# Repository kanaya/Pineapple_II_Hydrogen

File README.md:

# Pineapple II Hydrogen and Deuterium

## Description

Pineapple II Hydrogen (H) and Deuterium (2H) are a very simple MIDI sender/receiver. Pineapple II Hydrogen maps analog input from 0V to 5V to MIDI signal, and Pineapple II Deuterium converts MIDI signal to electrical status.

### Pineapple II Hydrogen (H)

### Pineapple II Deuterium (2H)

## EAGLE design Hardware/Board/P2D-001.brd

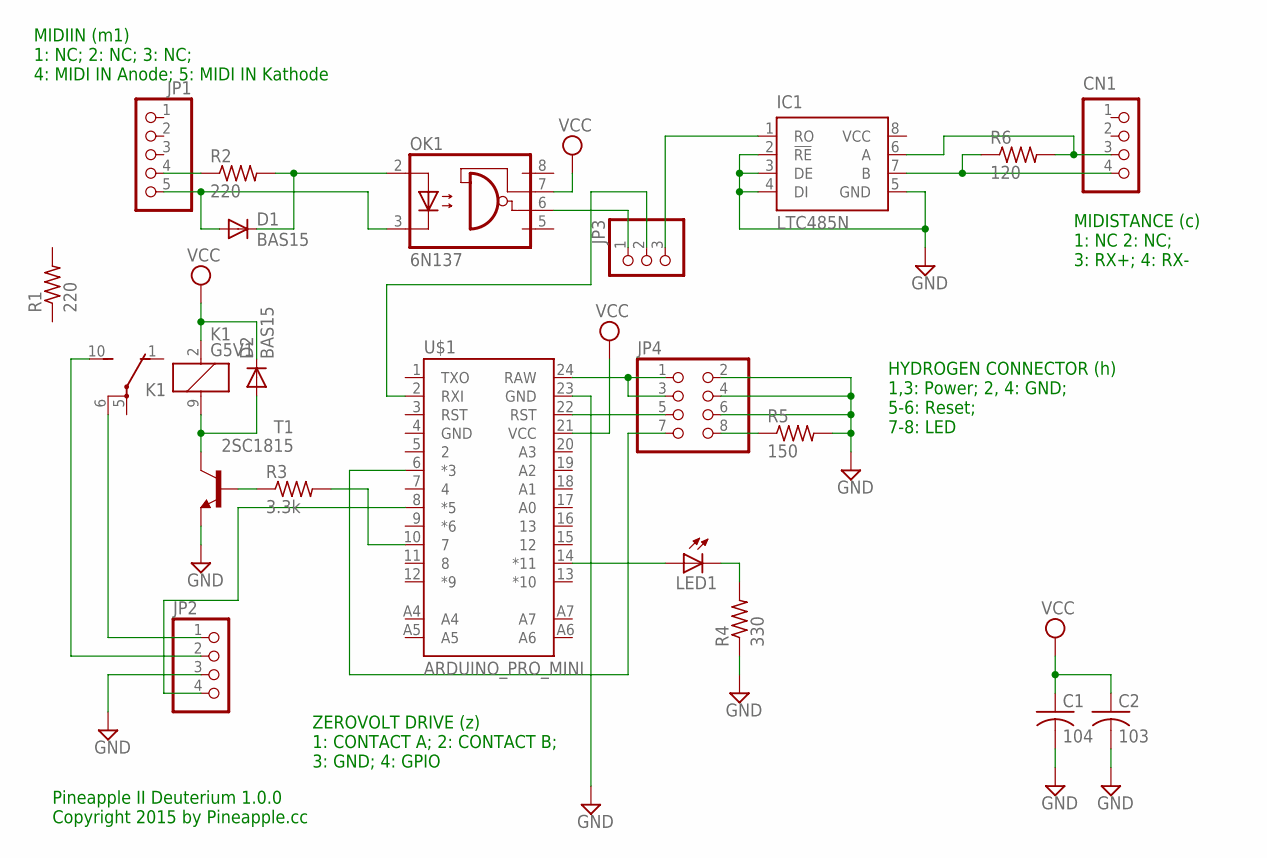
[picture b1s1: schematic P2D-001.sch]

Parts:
C1: 104; C025-025X050
C2: 103; C025-025X050
CN1: B4B-PH-K-S
D1, D2: BAS15; DO34-7
IC1: LTC485N; DIL08
JP1: PINHD-1X5; 1X05
JP2: PINHD-1X4; 1X04
JP3: PINHD-1X3; 1X03
JP4: PINHD-2X4; 2X04
K1: G5V1
LED1: LED3MM
OK1: 6N137; DIL08
R1, R2: 220; 0204/5
R3: 3.3k; 0204/5
R4: 330; 0204/5
R5: 150; 0204/5
R6: 120; 0204/5
T1: 2SC1815; TO92-ECB
U$1: ARDUINO_PRO_MINI

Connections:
GND: C1.2, C2.2, IC1.2 (!RE), IC1.3 (DE), IC1.4 (DI), IC1.5 (GND), JP2.3, JP4.2, JP4.4, JP4.6, R4.1, R5.2, T1.E, U$1.23 (GND)
unnamed: R3.2, U$1.10 (7)
unnamed: CN1.3, IC1.6 (A), R6.2
unnamed: JP1.4, R2.1
unnamed: D1.C, OK1.2 (A), R2.2
unnamed: JP4.8, R5.1
unnamed: JP4.5, U$1.22 (RST)
unnamed: D1.A, JP1.5, OK1.3 (C)
unnamed: JP4.7, U$1.6 (*3)
unnamed: JP4.1, JP4.3, U$1.24 (RAW)
unnamed: JP2.4, U$1.8 (*5)
unnamed: CN1.4, IC1.7 (B), R6.1
unnamed: JP3.1, OK1.6 (VO)
unnamed: R3.1, T1.B
unnamed: IC1.1 (RO), JP3.3
unnamed: D2.A, K1.9 (2), T1.C
unnamed: LED1.A, U$1.14 (*11)
unnamed: LED1.K (C), R4.2
unnamed: JP2.1, K1.6
unnamed: JP2.2, K1.10 (S)
unnamed: JP3.2, U$1.2 (RXI)
VCC: C1.1, C2.1, D2.C, K1.2 (1), OK1.7 (VE), U$1.21 (VCC)

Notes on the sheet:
Pineapple II Deuterium 1.0.0 Copyright 2015 by Pineapple.cc
MIDISTANCE (c) 1: NC 2: NC; 3: RX+; 4: RX-
MIDIIN (m1) 1: NC; 2: NC; 3: NC; 4: MIDI IN Anode; 5: MIDI IN Kathode
HYDROGEN CONNECTOR (h) 1,3: Power; 2, 4: GND; 5-6: Reset; 7-8: LED
ZEROVOLT DRIVE (z) 1: CONTACT A; 2: CONTACT B; 3: GND; 4: GPIO

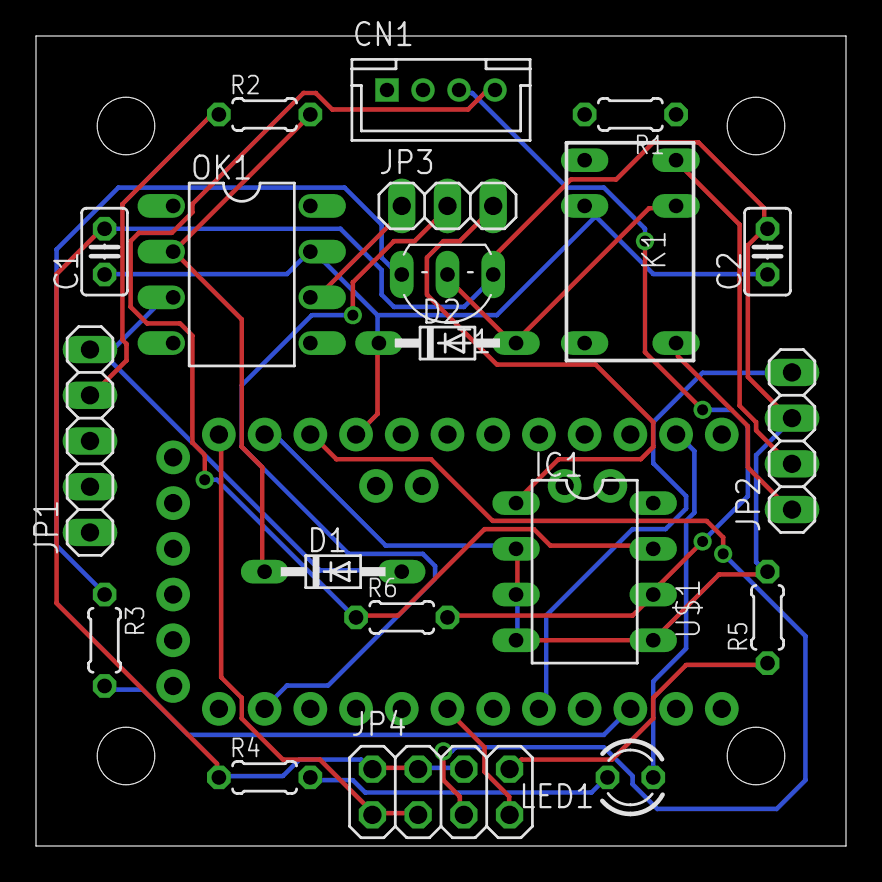
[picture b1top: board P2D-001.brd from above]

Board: 2 copper layers, 45.0 x 45.0 mm, 21 parts (0 on the bottom side), 22 nets.

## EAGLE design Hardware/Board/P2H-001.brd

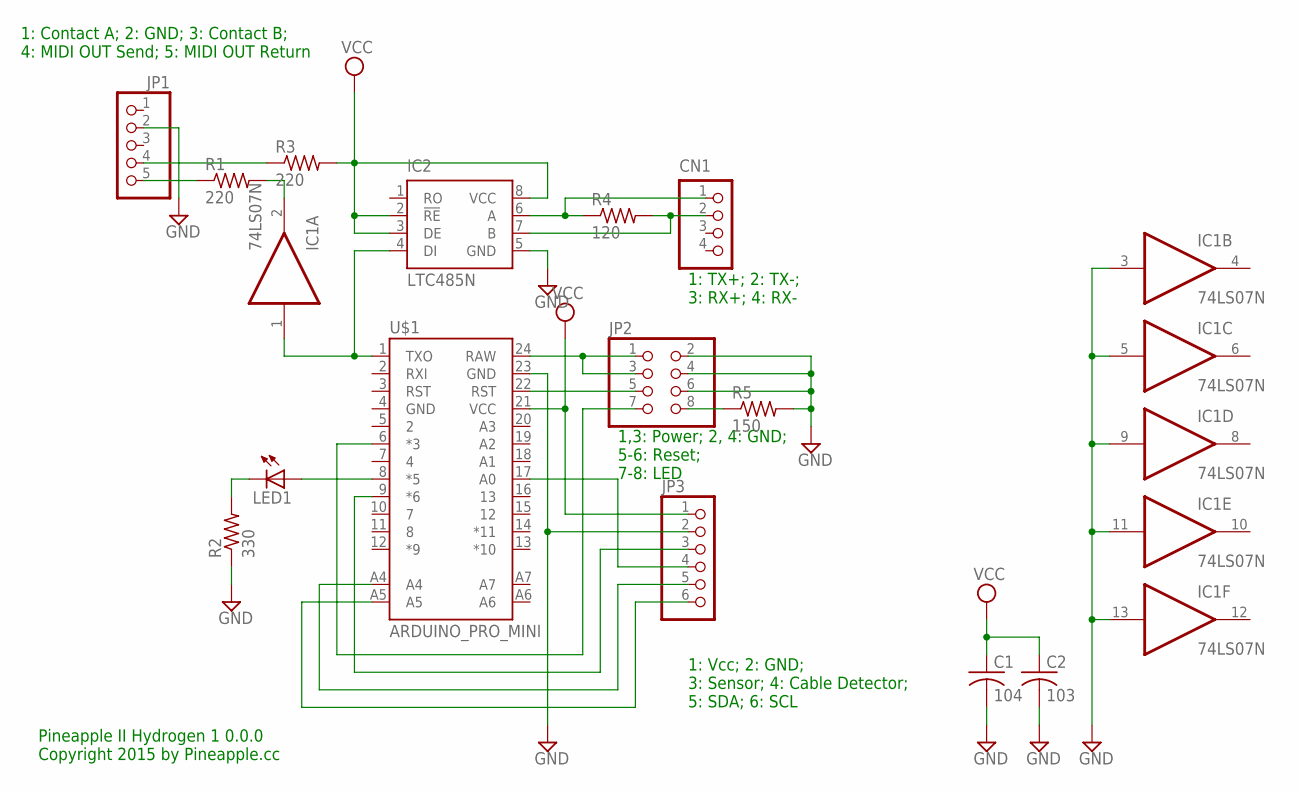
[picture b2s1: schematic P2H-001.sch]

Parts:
C1: 104; C025-025X050
C2: 103; C025-025X050
CN1: B4B-PH-K-S
IC1: 74LS07N; DIL14
IC2: LTC485N; DIL08
JP1: PINHD-1X5; 1X05
JP2: PINHD-2X4; 2X04
JP3: PINHD-1X6; 1X06
LED1: LED3MM
R1, R3: 220; 0204/5
R2: 330; 0204/5
R4: 120; 0204/5
R5: 150; 0204/5
U$1: ARDUINO_PRO_MINI

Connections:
GND: C1.2, C2.2, IC1.3 (I), IC1.5 (I), IC1.7 (GND), IC1.9 (I), IC1.11 (I), IC1.13 (I), IC2.5 (GND), JP1.2, JP2.2, JP2.4, JP2.6, JP3.2, R2.1, R5.2, U$1.23 (GND)
unnamed: IC1.1 (I), IC2.4 (DI), U$1.1 (TXO)
unnamed: IC1.2 (O), R1.2
unnamed: JP1.4, R3.1
unnamed: JP3.4, U$1.17 (A0)
unnamed: JP2.8, R5.1
unnamed: JP2.5, U$1.22 (RST)
unnamed: JP1.5, R1.1
unnamed: JP2.7, U$1.6 (*3)
unnamed: JP2.1, JP2.3, U$1.24 (RAW)
unnamed: JP3.3, U$1.9 (*6)
unnamed: JP3.5, U$1.A4
unnamed: LED1.A, U$1.8 (*5)
unnamed: LED1.K (C), R2.2
unnamed: JP3.6, U$1.A5
unnamed: CN1.1, IC2.6 (A), R4.1
unnamed: CN1.2, IC2.7 (B), R4.2
VCC: C1.1, C2.1, IC1.14 (VCC), IC2.2 (!RE), IC2.3 (DE), IC2.8 (VCC), JP3.1, R3.2, U$1.21 (VCC)

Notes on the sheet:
Pineapple II Hydrogen 1 0.0.0 Copyright 2015 by Pineapple.cc
1: TX+; 2: TX-; 3: RX+; 4: RX-
1: Contact A; 2: GND; 3: Contact B; 4: MIDI OUT Send; 5: MIDI OUT Return
1,3: Power; 2, 4: GND; 5-6: Reset; 7-8: LED
1: Vcc; 2: GND; 3: Sensor; 4: Cable Detector; 5: SDA; 6: SCL

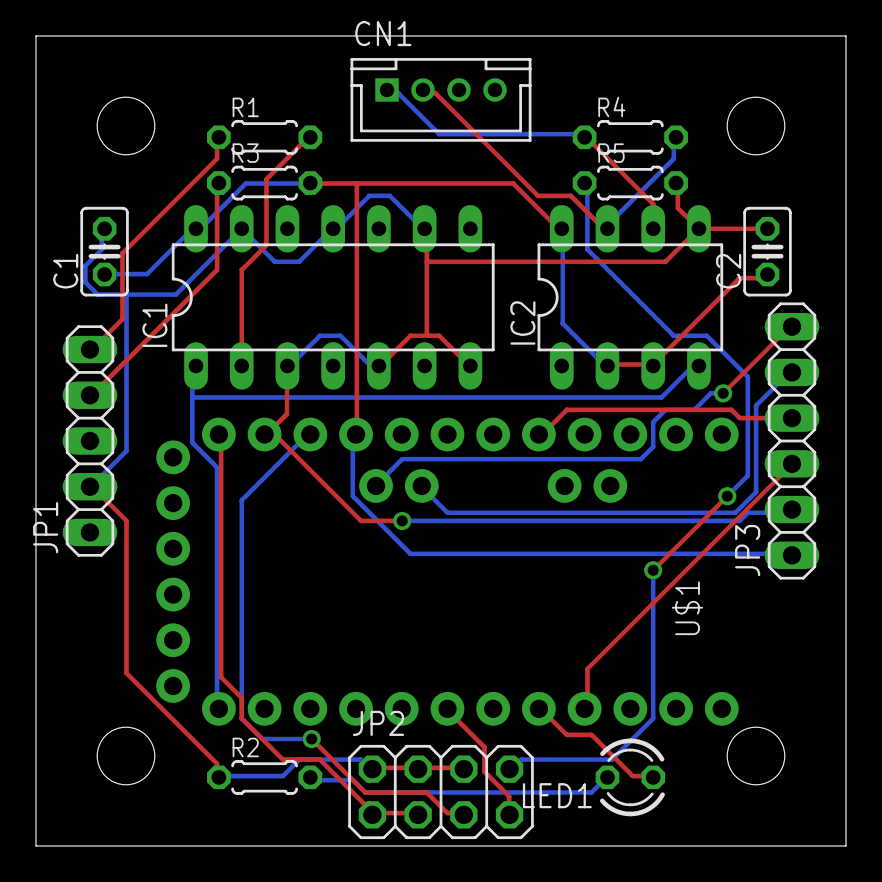
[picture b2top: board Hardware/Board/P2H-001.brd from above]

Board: 2 copper layers, 45.0 x 45.0 mm, 15 parts (0 on the bottom side), 18 nets.

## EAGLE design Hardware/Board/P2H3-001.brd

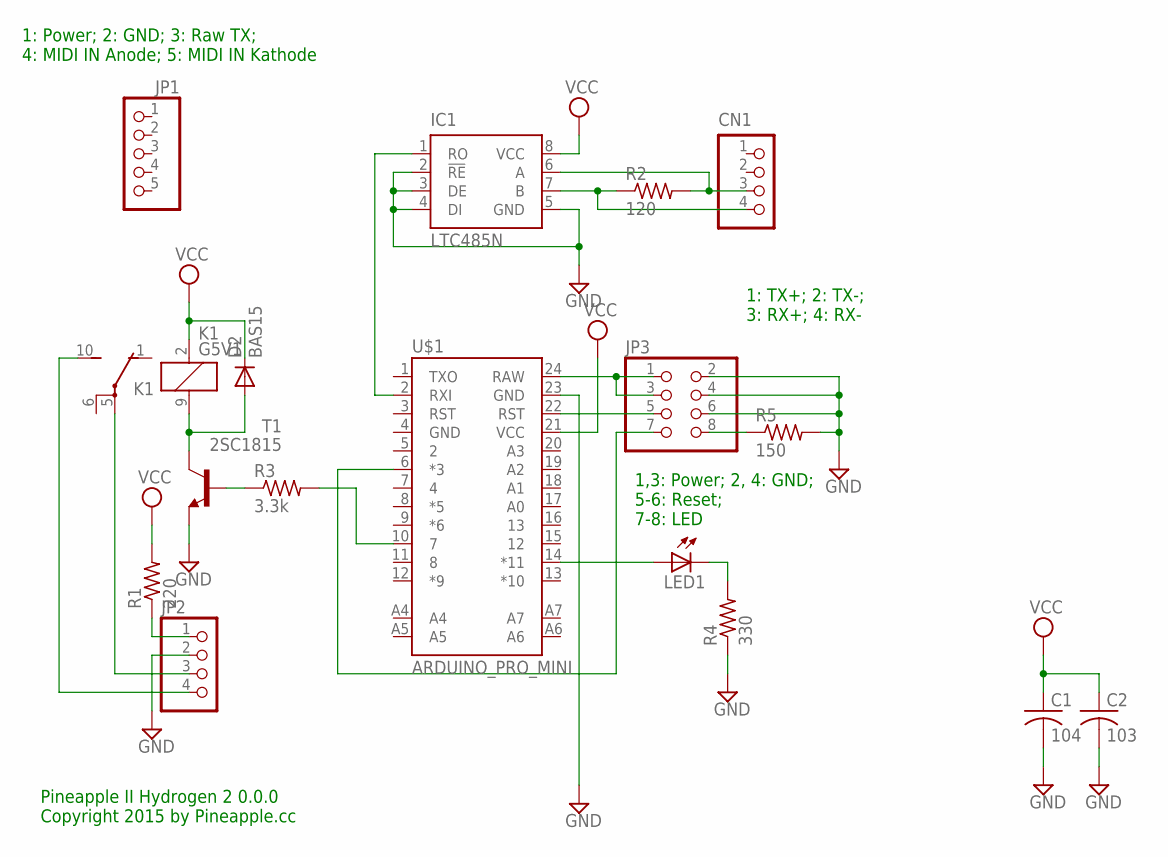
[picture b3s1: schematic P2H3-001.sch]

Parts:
C1: 104; C025-025X050
C2: 103; C025-025X050
CN1: B4B-PH-K-S
D2: BAS15; DO34-7
IC1: LTC485N; DIL08
JP1: PINHD-1X5; 1X05
JP2: PINHD-1X4; 1X04
JP3: PINHD-2X4; 2X04
K1: G5V1
LED1: LED3MM
R1: 220; 0204/5
R2: 120; 0204/5
R3: 3.3k; 0204/5
R4: 330; 0204/5
R5: 150; 0204/5
T1: 2SC1815; TO92-ECB
U$1: ARDUINO_PRO_MINI

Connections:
GND: C1.2, C2.2, IC1.2 (!RE), IC1.3 (DE), IC1.4 (DI), IC1.5 (GND), JP2.2, JP3.2, JP3.4, JP3.6, R4.1, R5.2, T1.E, U$1.23 (GND)
unnamed: R3.2, U$1.10 (7)
unnamed: CN1.3, IC1.6 (A), R2.2
unnamed: CN1.4, IC1.7 (B), R2.1
unnamed: JP3.8, R5.1
unnamed: JP3.5, U$1.22 (RST)
unnamed: JP3.7, U$1.6 (*3)
unnamed: JP3.1, JP3.3, U$1.24 (RAW)
unnamed: JP2.1, R1.1
unnamed: IC1.1 (RO), U$1.2 (RXI)
unnamed: R3.1, T1.B
unnamed: D2.A, K1.9 (2), T1.C
unnamed: LED1.A, U$1.14 (*11)
unnamed: LED1.K (C), R4.2
unnamed: JP2.3, K1.5
unnamed: JP2.4, K1.10 (S)
VCC: C1.1, C2.1, D2.C, IC1.8 (VCC), K1.2 (1), R1.2, U$1.21 (VCC)

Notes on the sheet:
Pineapple II Hydrogen 2 0.0.0 Copyright 2015 by Pineapple.cc
1: TX+; 2: TX-; 3: RX+; 4: RX-
1: Power; 2: GND; 3: Raw TX; 4: MIDI IN Anode; 5: MIDI IN Kathode
1,3: Power; 2, 4: GND; 5-6: Reset; 7-8: LED

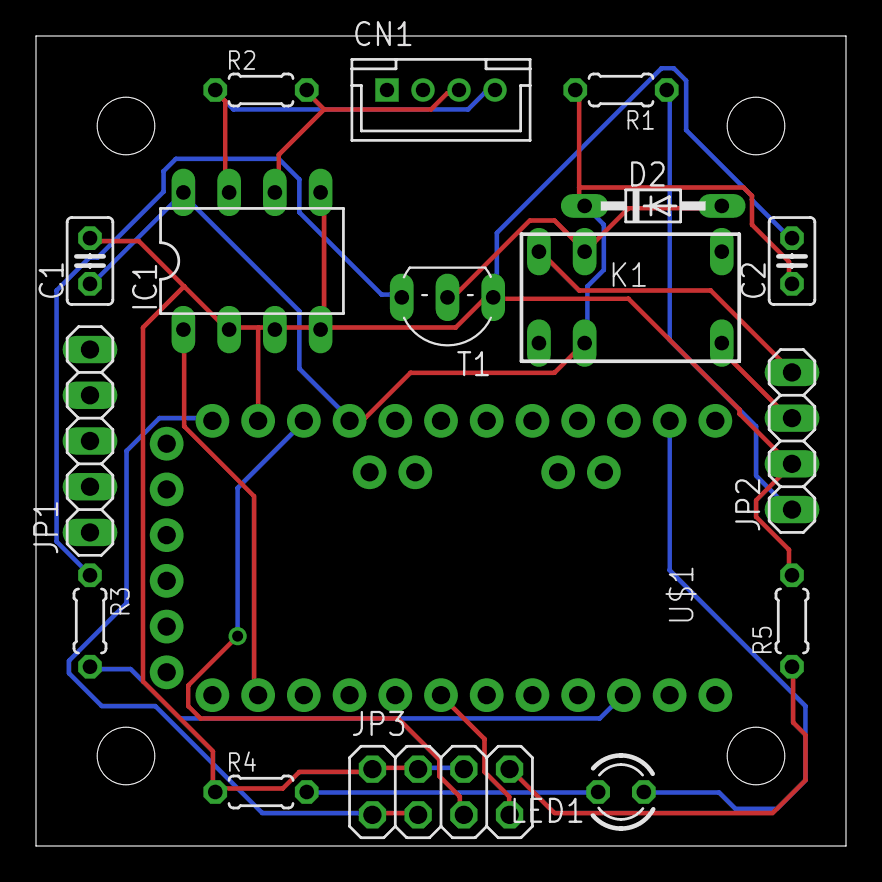
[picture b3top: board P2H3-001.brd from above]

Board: 2 copper layers, 45.0 x 45.0 mm, 17 parts (0 on the bottom side), 17 nets.

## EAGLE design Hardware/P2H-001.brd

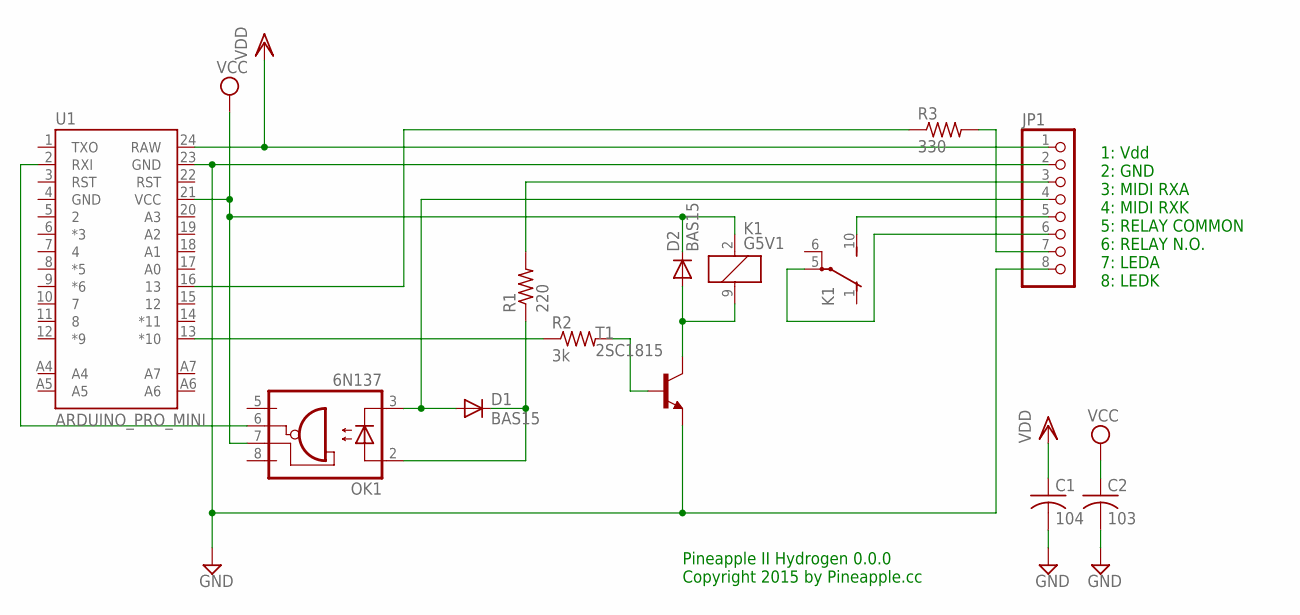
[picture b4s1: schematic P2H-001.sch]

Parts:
C1: 104; C025-025X050
C2: 103; C025-025X050
D1, D2: BAS15; DO34-7
JP1: PINHD-1X8; 1X08
K1: G5V1
OK1: 6N137; DIL08
R1: 220; 0204/5
R2: 3k; 0204/5
R3: 330; 0204/5
T1: 2SC1815; TO92-ECB
U1: ARDUINO_PRO_MINI

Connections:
GND: C1.2, C2.2, JP1.2, JP1.8, T1.E, U1.23 (GND)
MIDI0: JP1.3, R1.2
MIDI1: D1.A, JP1.4, OK1.3 (C)
unnamed: JP1.5, K1.10 (S)
unnamed: D2.A, K1.9 (2), T1.C
unnamed: R2.1, U1.13 (*10)
unnamed: R2.2, T1.B
unnamed: JP1.6, K1.5
unnamed: R3.1, U1.16 (13)
unnamed: JP1.7, R3.2
unnamed: D1.C, OK1.2 (A), R1.1
RX: OK1.6 (VO), U1.2 (RXI)
VCC: C2.1, D2.C, K1.2 (1), OK1.7 (VE), U1.21 (VCC)
VDD: C1.1, JP1.1, U1.24 (RAW)

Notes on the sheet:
Pineapple II Hydrogen 0.0.0 Copyright 2015 by Pineapple.cc
1: Vdd 2: GND 3: MIDI RXA 4: MIDI RXK 5: RELAY COMMON 6: RELAY N.O. 7: LEDA 8: LEDK

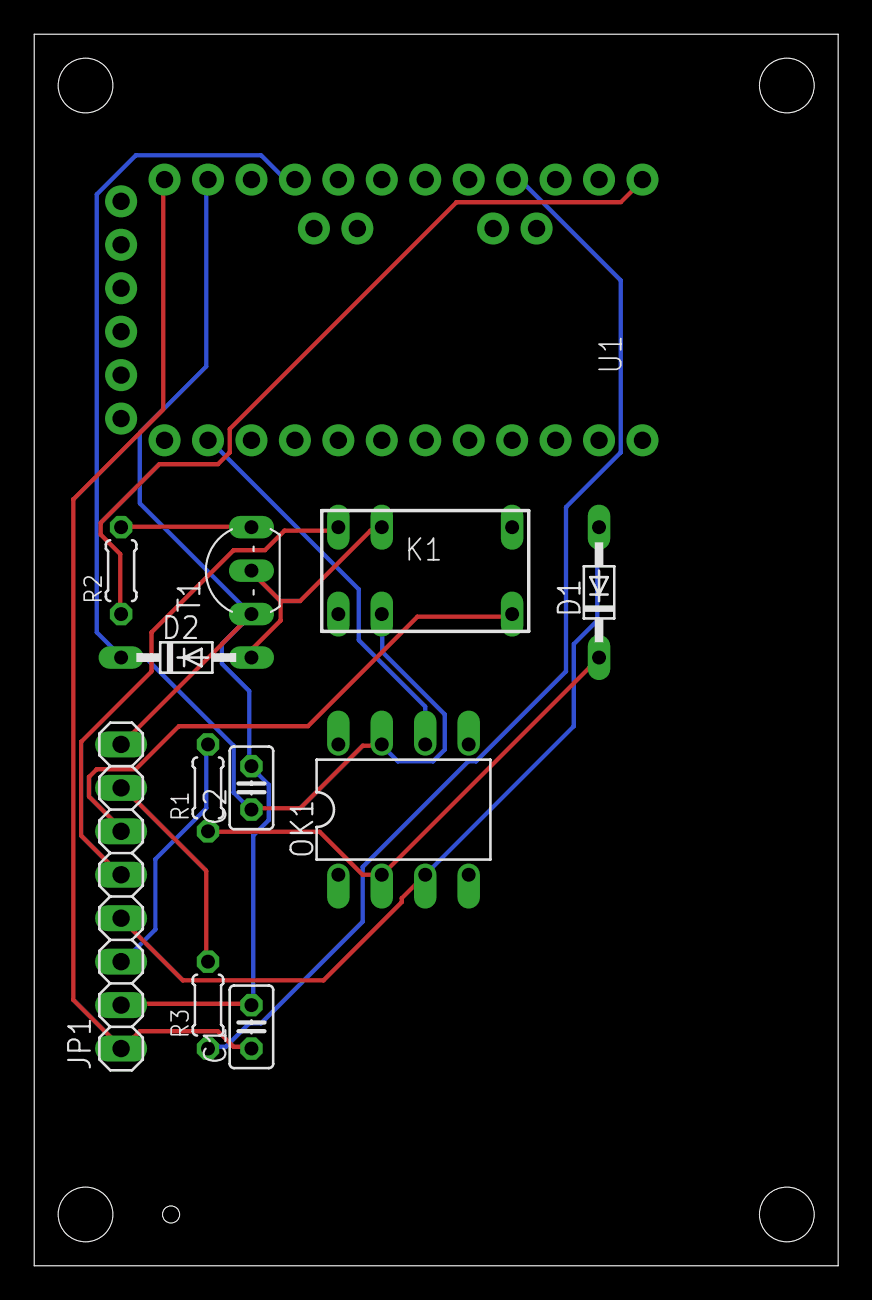
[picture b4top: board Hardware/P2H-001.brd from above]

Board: 2 copper layers, 47.0 x 72.0 mm, 12 parts (0 on the bottom side), 14 nets.

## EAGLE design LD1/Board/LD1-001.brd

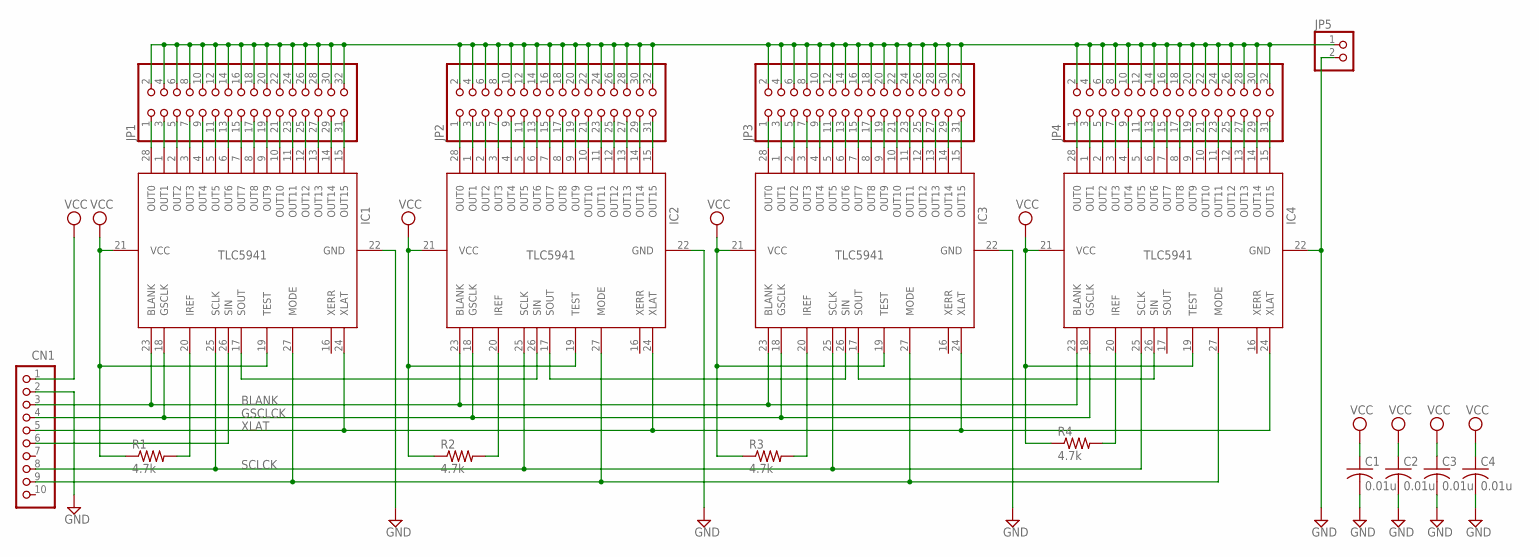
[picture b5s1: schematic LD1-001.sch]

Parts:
C1, C2, C3, C4: 0.01u; C025-025X050
CN1: S10B-PH-K-S
IC1, IC2, IC3, IC4: TLC5941NT; DIL28-3
JP1, JP2, JP3, JP4: PINHD-2X16; 2X16
JP5: PINHD-1X2; 1X02
R1, R2, R3, R4: 4.7k; 0204/5

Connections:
BLANK: CN1.3, IC1.23 (BLANK), IC2.23 (BLANK), IC3.23 (BLANK), IC4.23 (BLANK)
GND: C1.2, C2.2, C3.2, C4.2, CN1.2, IC1.22 (GND), IC2.22 (GND), IC3.22 (GND), IC4.22 (GND), JP5.2
GSCLCK: CN1.4, IC1.18 (GSCLK), IC2.18 (GSCLK), IC3.18 (GSCLK), IC4.18 (GSCLK)
unnamed: CN1.6, IC1.26 (SIN)
unnamed: IC1.17 (SOUT), IC2.26 (SIN)
unnamed: IC2.17 (SOUT), IC3.26 (SIN)
unnamed: IC3.17 (SOUT), IC4.26 (SIN)
unnamed: IC1.28 (OUT0), JP1.1
unnamed: IC1.1 (OUT1), JP1.3
unnamed: IC1.2 (OUT2), JP1.5
unnamed: IC1.3 (OUT3), JP1.7
unnamed: IC1.4 (OUT4), JP1.9
unnamed: IC1.5 (OUT5), JP1.11
unnamed: IC1.6 (OUT6), JP1.13
unnamed: IC1.7 (OUT7), JP1.15
unnamed: IC1.8 (OUT8), JP1.17
unnamed: IC1.9 (OUT9), JP1.19
unnamed: IC1.10 (OUT10), JP1.21
unnamed: IC1.11 (OUT11), JP1.23
unnamed: IC1.12 (OUT12), JP1.25
unnamed: IC1.13 (OUT13), JP1.27
unnamed: IC1.14 (OUT14), JP1.29
unnamed: IC1.15 (OUT15), JP1.31
unnamed: IC2.28 (OUT0), JP2.1
unnamed: IC2.1 (OUT1), JP2.3
unnamed: IC2.2 (OUT2), JP2.5
unnamed: IC2.3 (OUT3), JP2.7
unnamed: IC2.4 (OUT4), JP2.9
unnamed: IC2.5 (OUT5), JP2.11
unnamed: IC2.6 (OUT6), JP2.13
unnamed: IC2.7 (OUT7), JP2.15
unnamed: IC2.8 (OUT8), JP2.17
unnamed: IC2.9 (OUT9), JP2.19
unnamed: IC2.10 (OUT10), JP2.21
unnamed: IC2.11 (OUT11), JP2.23
unnamed: IC2.12 (OUT12), JP2.25
unnamed: IC2.13 (OUT13), JP2.27
unnamed: IC2.14 (OUT14), JP2.29
unnamed: IC2.15 (OUT15), JP2.31
unnamed: IC4.20 (IREF), R4.2
unnamed: IC3.28 (OUT0), JP3.1
unnamed: IC3.1 (OUT1), JP3.3
unnamed: IC3.2 (OUT2), JP3.5
unnamed: IC3.3 (OUT3), JP3.7
unnamed: IC3.4 (OUT4), JP3.9
unnamed: IC3.5 (OUT5), JP3.11
unnamed: IC3.6 (OUT6), JP3.13
unnamed: IC3.7 (OUT7), JP3.15
unnamed: IC2.20 (IREF), R2.2
unnamed: IC3.20 (IREF), R3.2
unnamed: IC3.8 (OUT8), JP3.17
unnamed: IC3.9 (OUT9), JP3.19
unnamed: IC3.10 (OUT10), JP3.21
unnamed: IC3.11 (OUT11), JP3.23
unnamed: IC3.12 (OUT12), JP3.25
unnamed: IC3.13 (OUT13), JP3.27
unnamed: IC3.14 (OUT14), JP3.29
unnamed: IC3.15 (OUT15), JP3.31
unnamed: IC4.28 (OUT0), JP4.1
unnamed: IC4.1 (OUT1), JP4.3
unnamed: IC4.2 (OUT2), JP4.5
unnamed: IC4.3 (OUT3), JP4.7
unnamed: IC4.4 (OUT4), JP4.9
unnamed: IC4.5 (OUT5), JP4.11
unnamed: IC4.6 (OUT6), JP4.13
unnamed: IC4.7 (OUT7), JP4.15
unnamed: IC4.8 (OUT8), JP4.17
unnamed: IC1.20 (IREF), R1.2
unnamed: IC4.9 (OUT9), JP4.19
unnamed: IC4.10 (OUT10), JP4.21
unnamed: IC4.11 (OUT11), JP4.23
unnamed: IC4.12 (OUT12), JP4.25
unnamed: IC4.13 (OUT13), JP4.27
unnamed: IC4.14 (OUT14), JP4.29
unnamed: IC4.15 (OUT15), JP4.31
unnamed: JP1.2, JP1.4, JP1.6, JP1.8, JP1.10, JP1.12, JP1.14, JP1.16, JP1.18, JP1.20, JP1.22, JP1.24, JP1.26, JP1.28, JP1.30, JP1.32, JP2.2, JP2.4, JP2.6, JP2.8, JP2.10, JP2.12, JP2.14, JP2.16, JP2.18, JP2.20, JP2.22, JP2.24, JP2.26, JP2.28, JP2.30, JP2.32, JP3.2, JP3.4, JP3.6, JP3.8, JP3.10, JP3.12, JP3.14, JP3.16, JP3.18, JP3.20, JP3.22, JP3.24, JP3.26, JP3.28, JP3.30, JP3.32, JP4.2, JP4.4, JP4.6, JP4.8, JP4.10, JP4.12, JP4.14, JP4.16, JP4.18, JP4.20, JP4.22, JP4.24, JP4.26, JP4.28, JP4.30, JP4.32, JP5.1
unnamed: CN1.9, IC1.27 (MODE), IC2.27 (MODE), IC3.27 (MODE), IC4.27 (MODE)
SCLCK: CN1.8, IC1.25 (SCLK), IC2.25 (SCLK), IC3.25 (SCLK), IC4.25 (SCLK)
VCC: C1.1, C2.1, C3.1, C4.1, CN1.1, IC1.19 (TEST), IC1.21 (VCC), IC2.19 (TEST), IC2.21 (VCC), IC3.19 (TEST), IC3.21 (VCC), IC4.19 (TEST), IC4.21 (VCC), R1.1, R2.1, R3.1, R4.1
XLAT: CN1.5, IC1.24 (XLAT), IC2.24 (XLAT), IC3.24 (XLAT), IC4.24 (XLAT)

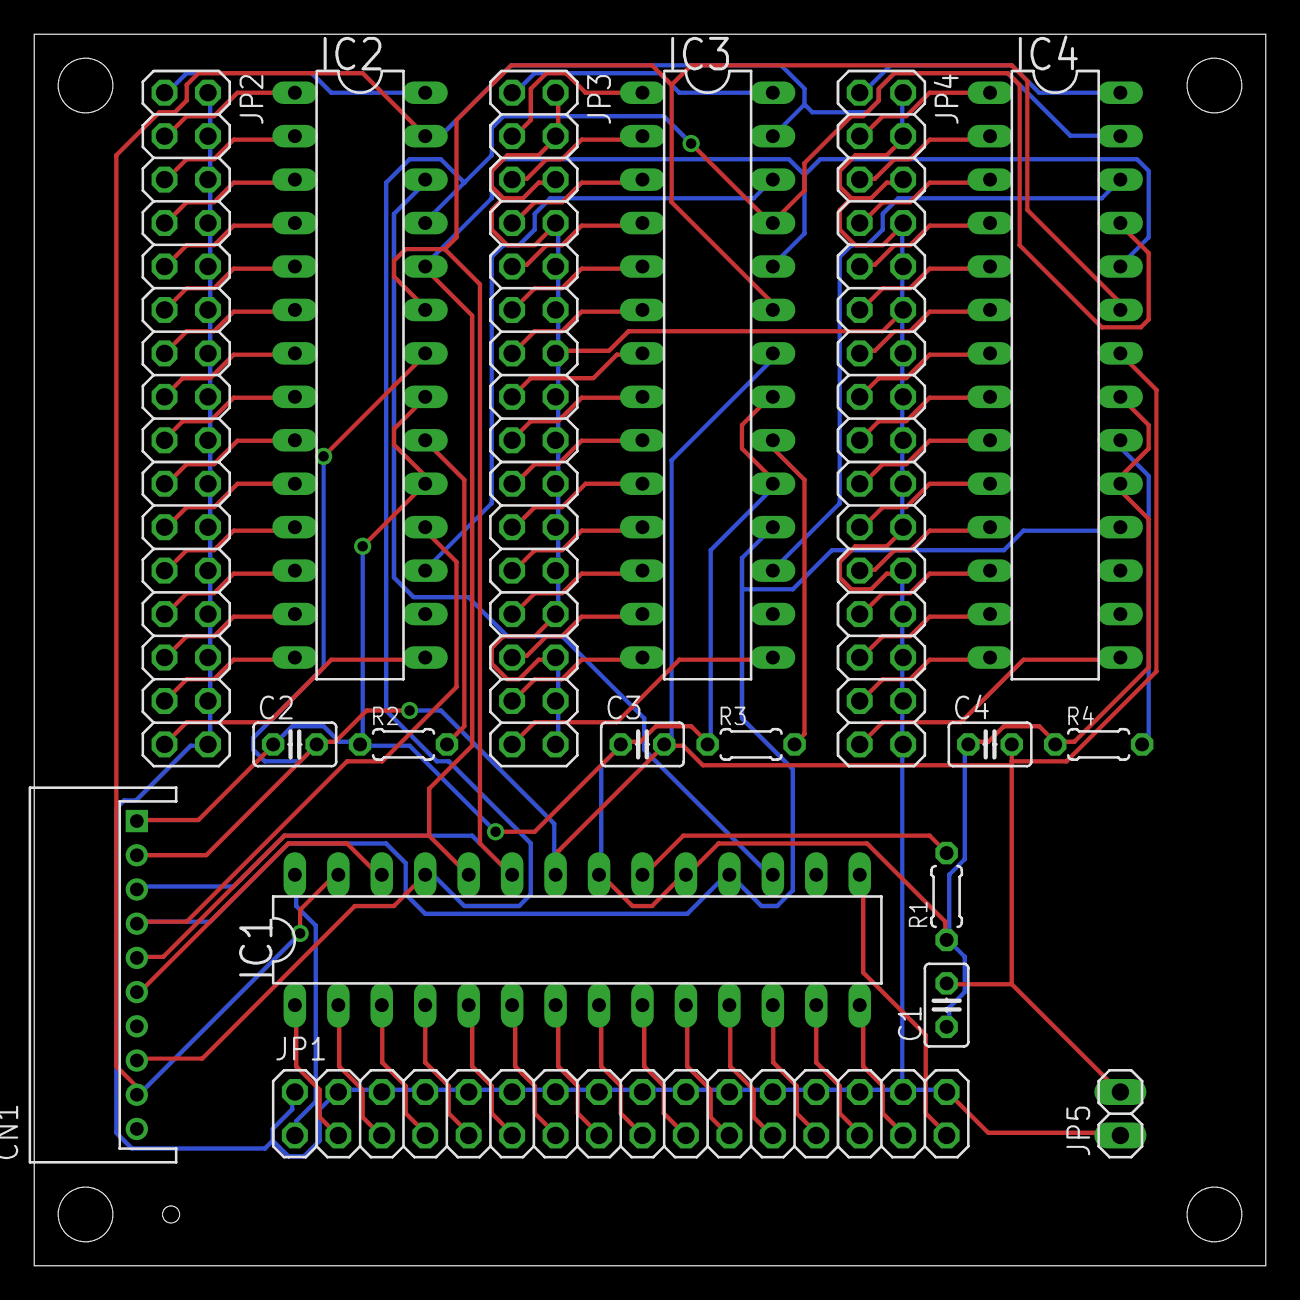
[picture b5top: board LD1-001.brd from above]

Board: 2 copper layers, 72.0 x 72.0 mm, 18 parts (0 on the bottom side), 80 nets.

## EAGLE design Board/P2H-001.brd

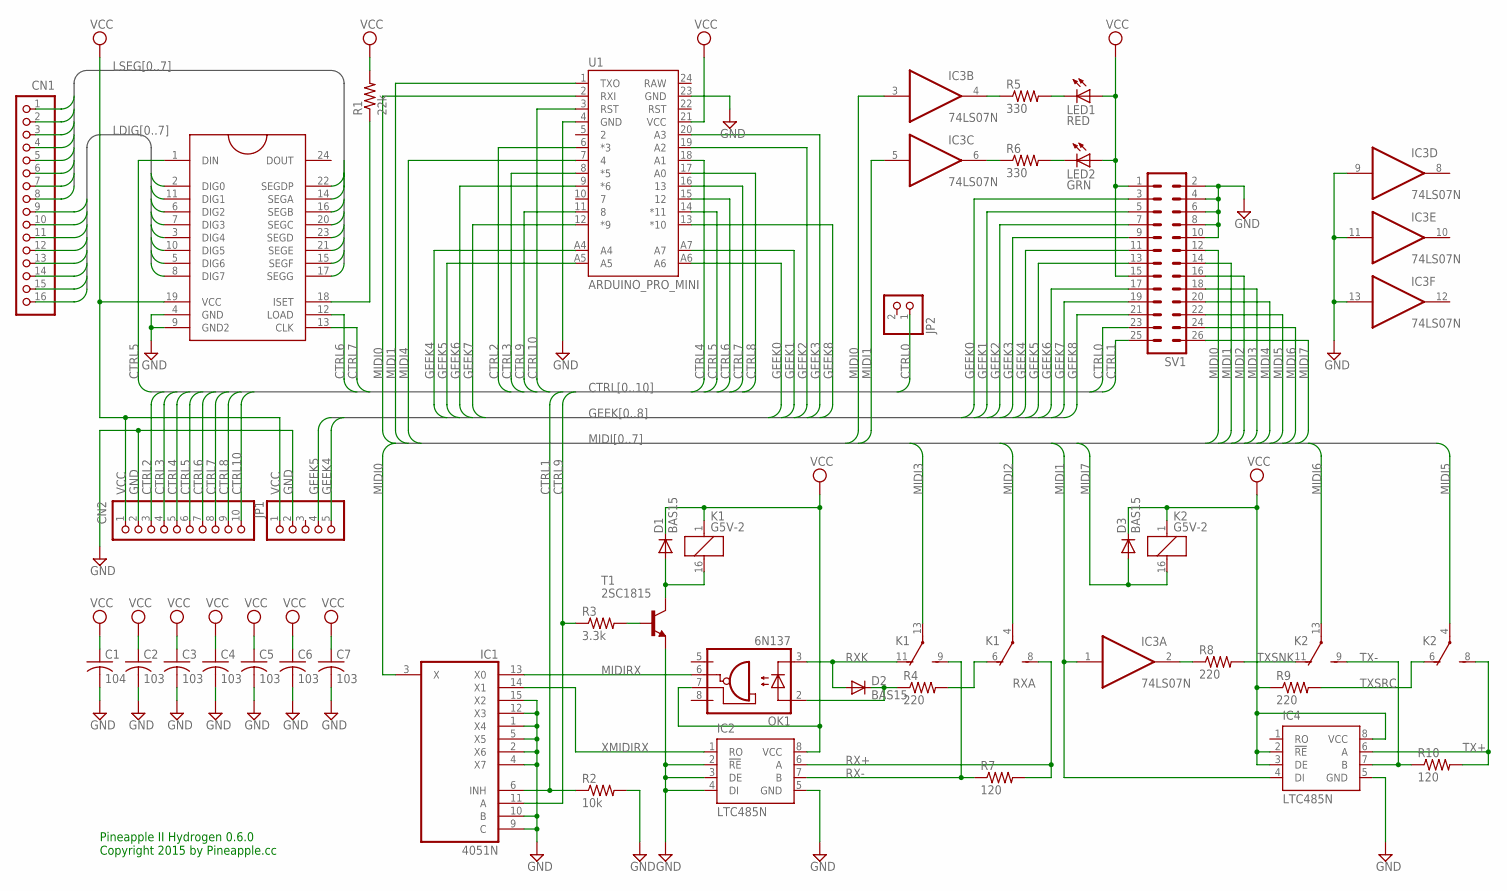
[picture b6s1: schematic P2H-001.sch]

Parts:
C1: 104; C025-025X050
C2, C3, C4, C5, C6, C7: 103; C025-025X050
CN1: S16B-PH-K-S
CN2: S10B-PH-K-S
D1, D2, D3: BAS15; DO34-7
IC1: 4051N; DIL16
IC2, IC4: LTC485N; DIL08
IC3: 74LS07N; DIL14
JP1: PINHD-1X5; 1X05
JP2: PINHD-1X2; 1X02
K1, K2: G5V-2
LED1: RED; LED3MM
LED2: GRN; LED3MM
OK1: 6N137; DIL08
R1: 22k; 0204/5
R2: 10k; 0204/5
R3: 3.3k; 0204/5
R4, R8, R9: 220; 0204/5
R5, R6: 330; 0204/5
R7, R10: 120; 0204/5
SV1: ML26L
T1: 2SC1815; TO92-ECB
U1: ARDUINO_PRO_MINI
U2: MAX7219DIP; DIL24

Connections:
CTRL0: JP2.1, SV1.23
CTRL1: IC1.6 (INH), R2.1, SV1.25
CTRL2: CN2.3, U1.6 (*3)
CTRL3: CN2.4, U1.8 (*5)
CTRL4: CN2.5, U1.18 (A1)
CTRL5: CN2.6, U1.14 (*11), U2.1 (DIN)
CTRL6: CN2.7, U1.15 (12), U2.12 (LOAD)
CTRL7: CN2.8, U1.16 (13), U2.13 (CLK)
CTRL8: CN2.9, U1.17 (A0)
CTRL9: IC1.11 (A), R3.1, U1.11 (8)
CTRL10: CN2.10, U1.3 (RST)
GEEK0: SV1.3, U1.A6
GEEK1: SV1.5, U1.A7
GEEK2: SV1.7, U1.19 (A2)
GEEK3: SV1.9, U1.20 (A3)
GEEK4: JP1.5, SV1.11, U1.A4
GEEK5: JP1.4, SV1.13, U1.A5
GEEK6: SV1.17, U1.9 (*6)
GEEK7: SV1.19, U1.12 (*9)
GEEK8: SV1.21, U1.13 (*10)
GND: C1.2, C2.2, C3.2, C4.2, C5.2, C6.2, C7.2, CN2.2, IC1.1 (X4), IC1.2 (X6), IC1.4 (X7), IC1.5 (X5), IC1.8 (GND), IC1.9 (C), IC1.10 (B), IC1.12 (X3), IC1.15 (X2), IC2.2 (!RE), IC2.3 (DE), IC2.4 (DI), IC2.5 (GND), IC3.7 (GND), IC3.9 (I), IC3.11 (I), IC3.13 (I), IC4.5 (GND), JP1.2, R2.2, SV1.2, SV1.4, SV1.6, SV1.8, SV1.10, T1.E, U1.4 (GND), U1.23 (GND), U2.4 (GND), U2.9 (GND2)
LDIG0: CN1.9, U2.2 (DIG0)
LDIG1: CN1.10, U2.11 (DIG1)
LDIG2: CN1.11, U2.6 (DIG2)
LDIG3: CN1.12, U2.7 (DIG3)
LDIG4: CN1.13, U2.3 (DIG4)
LDIG5: CN1.14, U2.10 (DIG5)
LDIG6: CN1.15, U2.5 (DIG6)
LDIG7: CN1.16, U2.8 (DIG7)
LSEG0: CN1.1, U2.22 (SEGDP)
LSEG1: CN1.2, U2.14 (SEGA)
LSEG2: CN1.3, U2.16 (SEGB)
LSEG3: CN1.4, U2.20 (SEGC)
LSEG4: CN1.5, U2.23 (SEGD)
LSEG5: CN1.6, U2.21 (SEGE)
LSEG6: CN1.7, U2.15 (SEGF)
LSEG7: CN1.8, U2.17 (SEGG)
MIDI0: IC1.3 (X), IC3.3 (I), SV1.12, U1.2 (RXI)
MIDI1: IC3.1 (I), IC3.5 (I), IC4.4 (DI), SV1.14, U1.1 (TXO)
MIDI2: K1.4, SV1.16
MIDI3: K1.13, SV1.18
MIDI4: SV1.20, U1.7 (4)
MIDI5: K2.4, SV1.22
MIDI6: K2.13, SV1.24
MIDI7: D3.A, K2.16 (2), SV1.26
MIDIRX: IC1.13 (X0), OK1.6 (VO)
unnamed: R3.2, T1.B
unnamed: IC3.2 (O), R8.1
unnamed: IC3.4 (O), R5.1
unnamed: IC3.6 (O), R6.1
unnamed: LED1.K (C), R5.2
unnamed: LED2.K (C), R6.2
unnamed: D1.A, K1.16 (2), T1.C
unnamed: D2.C, OK1.2 (A), R4.1
unnamed: R1.1, U2.18 (ISET)
RX+: IC2.6 (A), K1.8 (S), R7.2
RX-: IC2.7 (B), K1.9 (S), R7.1
RXA: K1.6 (O), R4.2
RXK: D2.A, K1.11 (O), OK1.3 (C)
TX+: IC4.6 (A), K2.8 (S), R10.2
TX-: IC4.7 (B), K2.9 (S), R10.1
TXSNK: K2.11 (O), R8.2
TXSRC: K2.6 (O), R9.2
VCC: C1.1, C2.1, C3.1, C4.1, C5.1, C6.1, C7.1, CN2.1, D1.C, D3.C, IC1.16 (VCC), IC2.8 (VCC), IC3.14 (VCC), IC4.2 (!RE), IC4.3 (DE), IC4.8 (VCC), JP1.1, K1.1, K2.1, LED1.A, LED2.A, OK1.7 (VE), R1.2, R9.1, SV1.1, SV1.15, U1.21 (VCC), U2.19 (VCC)
VEE: IC1.7 (VEE)
XMIDIRX: IC1.14 (X1), IC2.1 (RO)

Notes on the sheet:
Pineapple II Hydrogen 0.6.0 Copyright 2015 by Pineapple.cc

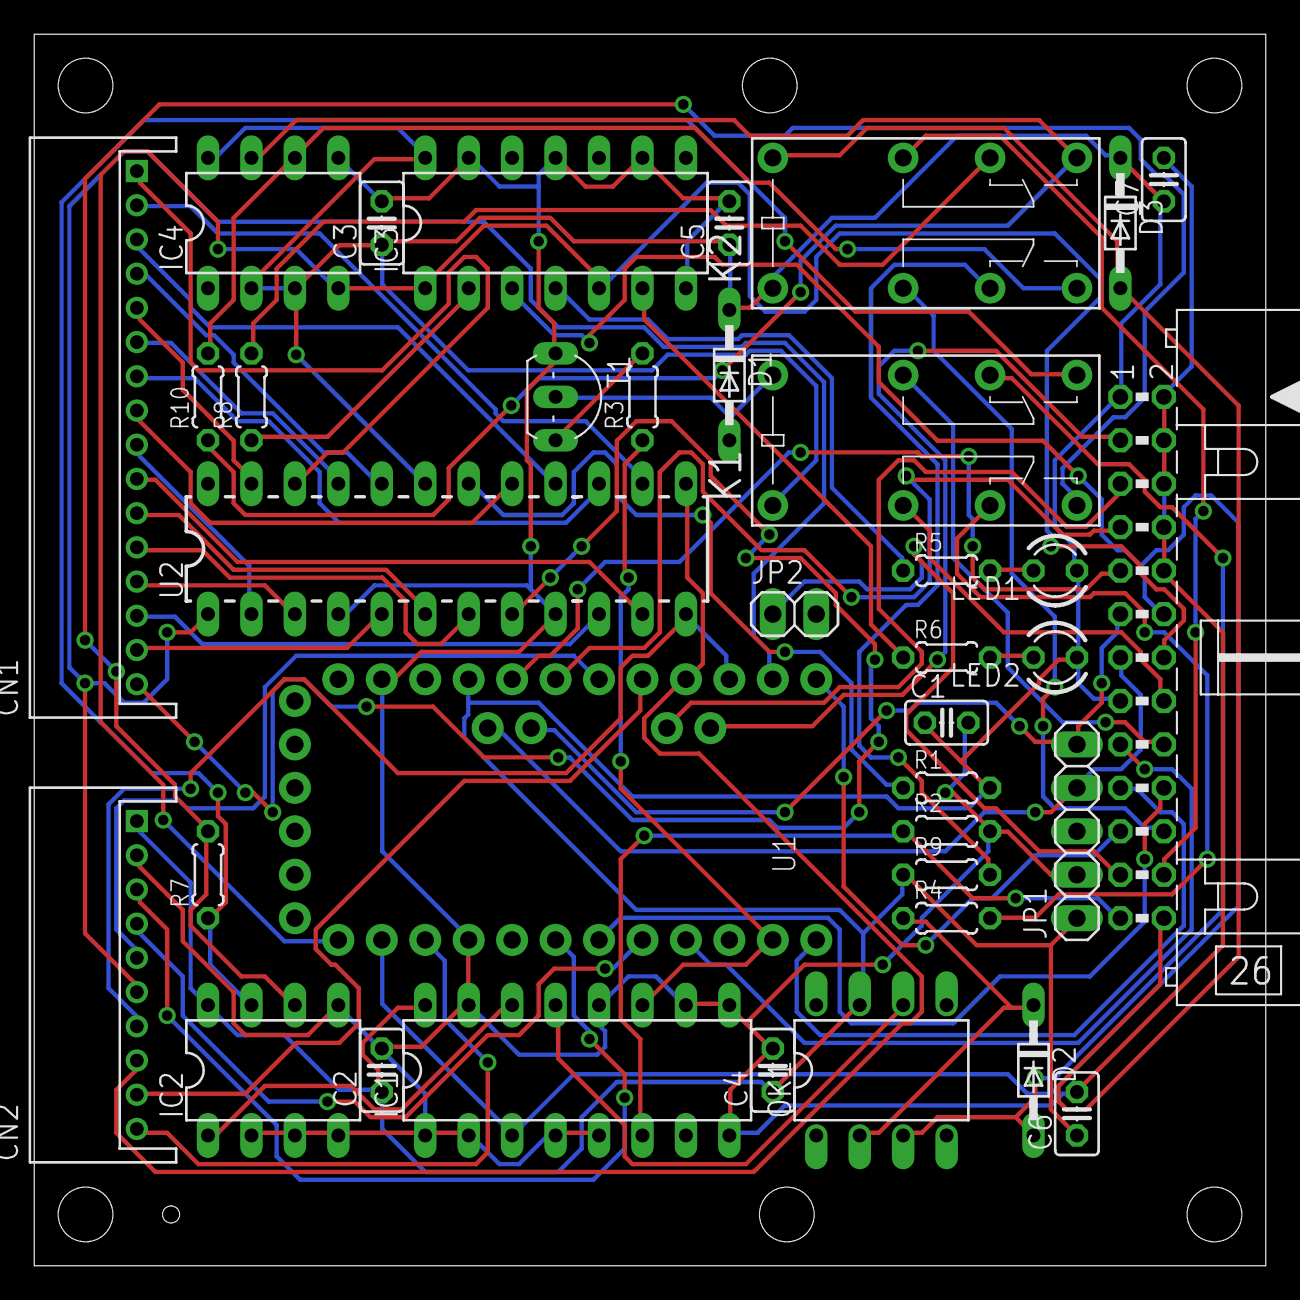
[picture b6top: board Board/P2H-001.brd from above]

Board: 2 copper layers, 72.0 x 72.0 mm, 37 parts (0 on the bottom side), 65 nets.

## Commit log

2015-01-16 Front and back panels.
2015-01-17 Now MIDI IN and OUT are both supported.
2015-01-17 Original cofiguration of Takachis case was added.
2015-01-17 Initial board design.
2015-01-17 Now it should work.
2015-01-17 Changed push button.
2015-01-17 Layout.
2015-01-17 Redesigned for ICB-93 size.
2015-01-17 Ready to autoroute.
2015-01-18 Design renewed.
2015-01-18 Slightly re-arranged.
2015-01-19 Autorouted.
2015-01-19 square design.
2015-01-19 Routed by 0.10mm paths.
2015-01-19 slightly optimized.
2015-01-19 Renamed parts.
2015-01-19 Images.
2015-01-20 Rearranged almost everything.
2015-01-20 fine tuning of board.
2015-01-20 Added holes.
2015-01-20 Renumbered parts.
2015-01-20 Tuning of routing.
2015-01-21 Now MIDI IN has detector connector.
2015-01-21 Now frontport is PH connector.
2015-01-21 Updated gitignore.
2015-01-22 fixed wiring.
2015-01-23 Updated image versions.
2015-01-28 One TLC.
2015-01-28 Label.
2015-01-28 re-arranged board.
2015-01-28 New design.
2015-01-28 Brush up.
2015-01-28 Hotfix.
2015-01-28 Added documents.
2015-01-28 Board and Doc update.
2015-01-28 Jumper to Switch.
2015-01-28 Added LD1 add-on board.
2015-01-28 document update.
2015-01-29 changed circuit of mdetect.
2015-01-29 .gitignore update.
2015-01-29 changed detector cicuits for midi in and out.
2015-01-29 Layout change.
2015-01-29 Image update.
2015-01-30 Fixed panel LED layout.
2015-01-30 9 LEDs.
2015-01-30 Renumbered LED numbers.
2015-02-04 Still updating.
2015-02-05 Autorouted 2.
2015-02-05 New drive port.
2015-02-05 Updating...
2015-02-05 Refine of sch.
2015-02-06 fine tuning.
2015-02-06 Refinement of panel and schematic.
2015-02-07 Before the first prototyping.
2015-02-07 fixed many problems.
2015-02-07 fixed doc.
2015-02-07 Updated images.
2015-02-08 Changed the positions of holes.
2015-02-09 new panel design.
2015-02-09 Refinement of schematic.
2015-02-17 New design for release 0.6.
2015-02-17 Renamed files.
2015-02-19 Develop for R0.6
2015-02-19 Now ready for R0.6.
2015-02-19 refine.
2015-02-20 minor correction.
2015-02-20 Renewed panel design.
2015-02-20 corrected errata.
2015-02-21 Removed D2 and D7.
2015-02-21 DrivePort 10 is now connected to RST.
2015-02-21 Updated LD1.
2015-03-20 clean up.
2015-03-21 fixed typo.
2015-03-21 another clean up.
2015-03-21 Initial commit.
2015-04-14 Directory change.
2015-04-14 New design. New implementatino.
2015-04-14 New board design.
2015-04-14 Added comments.
2015-04-16 Changed board size to 45mm x 45mm.
2015-04-16 Added case design.
2015-04-16 Updated README.
2015-04-16 Changed position of LED resistor.
2015-04-22 New pinout.
2015-04-22 Adopted to the new pinout.
2015-04-22 Adopted new Hydroport pinout.
2015-04-22 Added P2H2 model.
2015-04-22 Added Hydroport (HR10A 6p).
2015-04-22 Fixed connection error of MIDI IN.
2015-04-22 Adopted to Relayport.
2015-04-23 Changed layout of ZeroVoltage.
2015-04-23 Added H3 model.
2015-04-23 Merged H2 and H3.
2015-04-23 Removed H3 model.
2015-07-23 Overhaul.

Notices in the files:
parts and their libraries:
SparkFun-DigitalIC: Licensing: Creative Commons ShareAlike 4.0 International - https://creativecommons.org/licenses/by-sa/4.0
